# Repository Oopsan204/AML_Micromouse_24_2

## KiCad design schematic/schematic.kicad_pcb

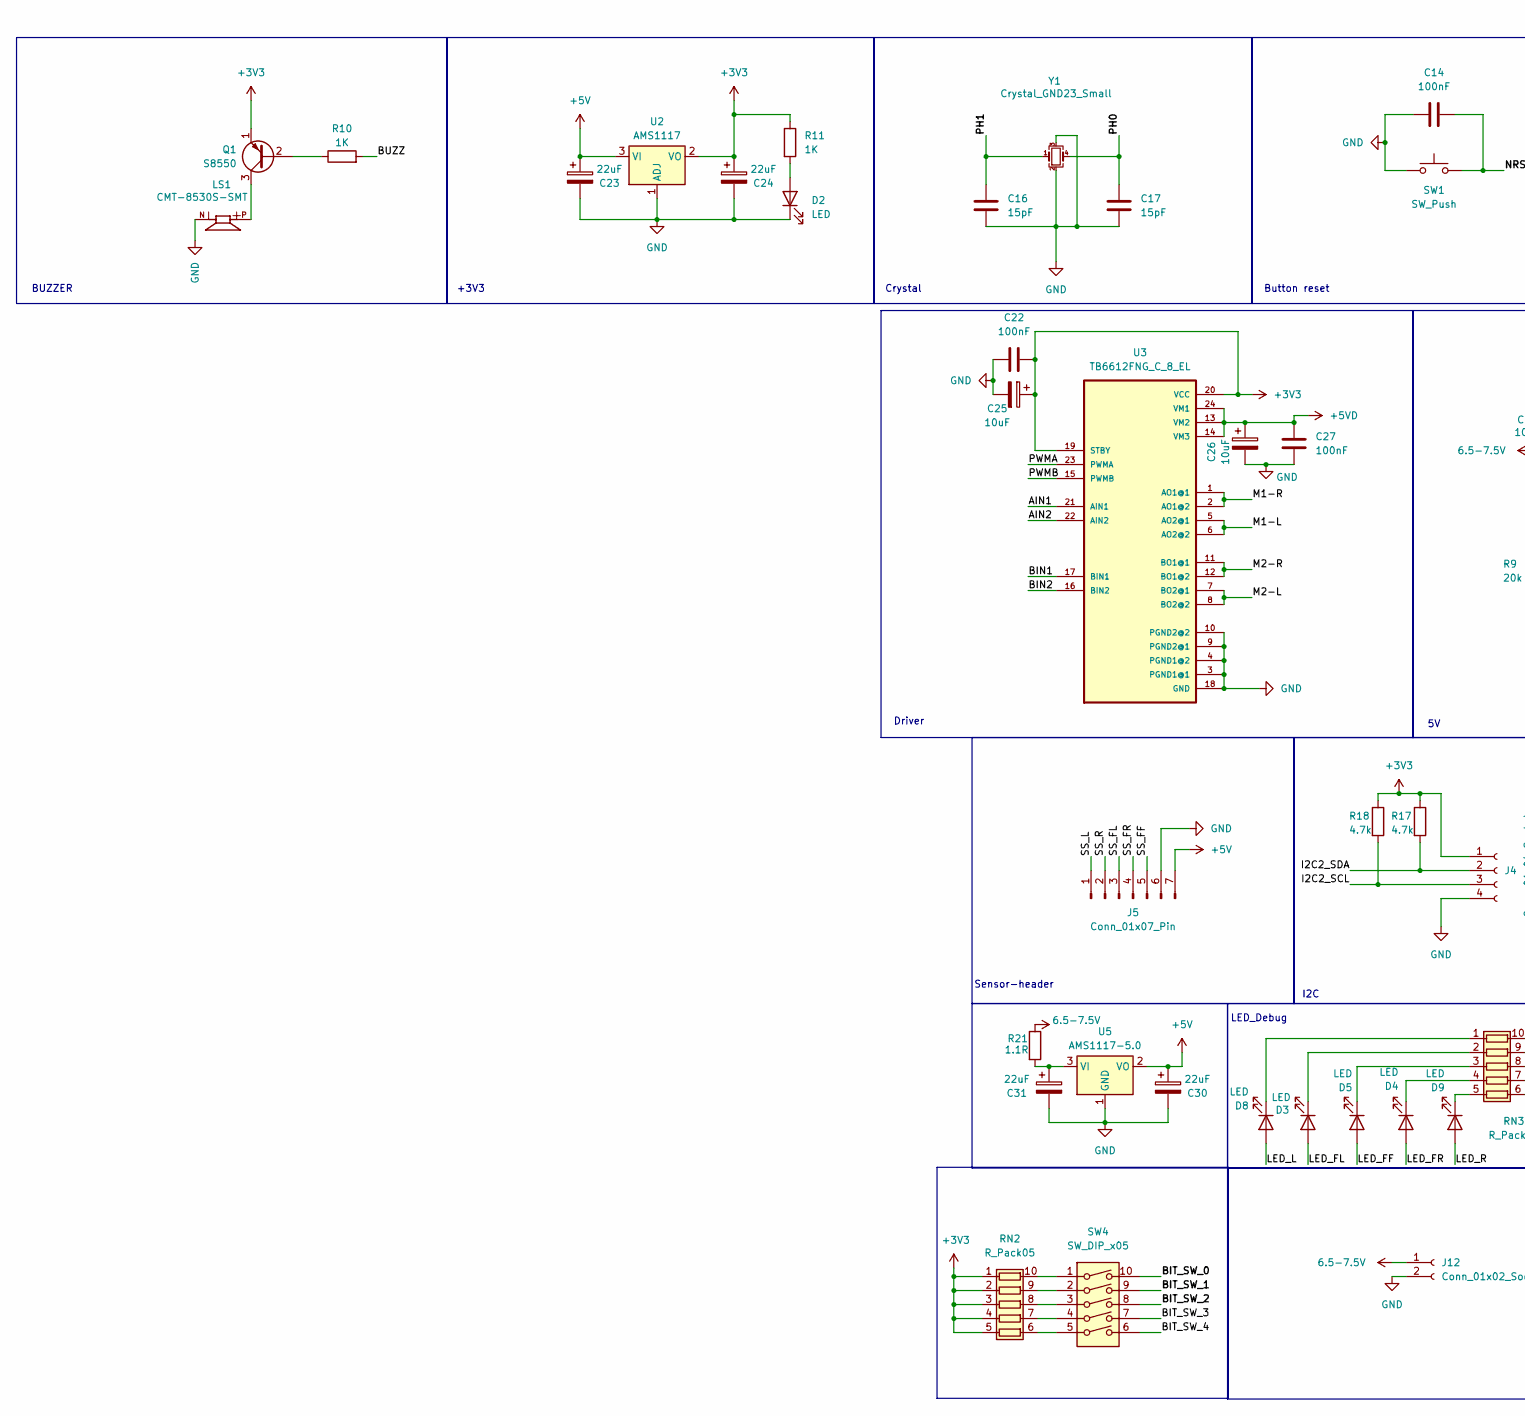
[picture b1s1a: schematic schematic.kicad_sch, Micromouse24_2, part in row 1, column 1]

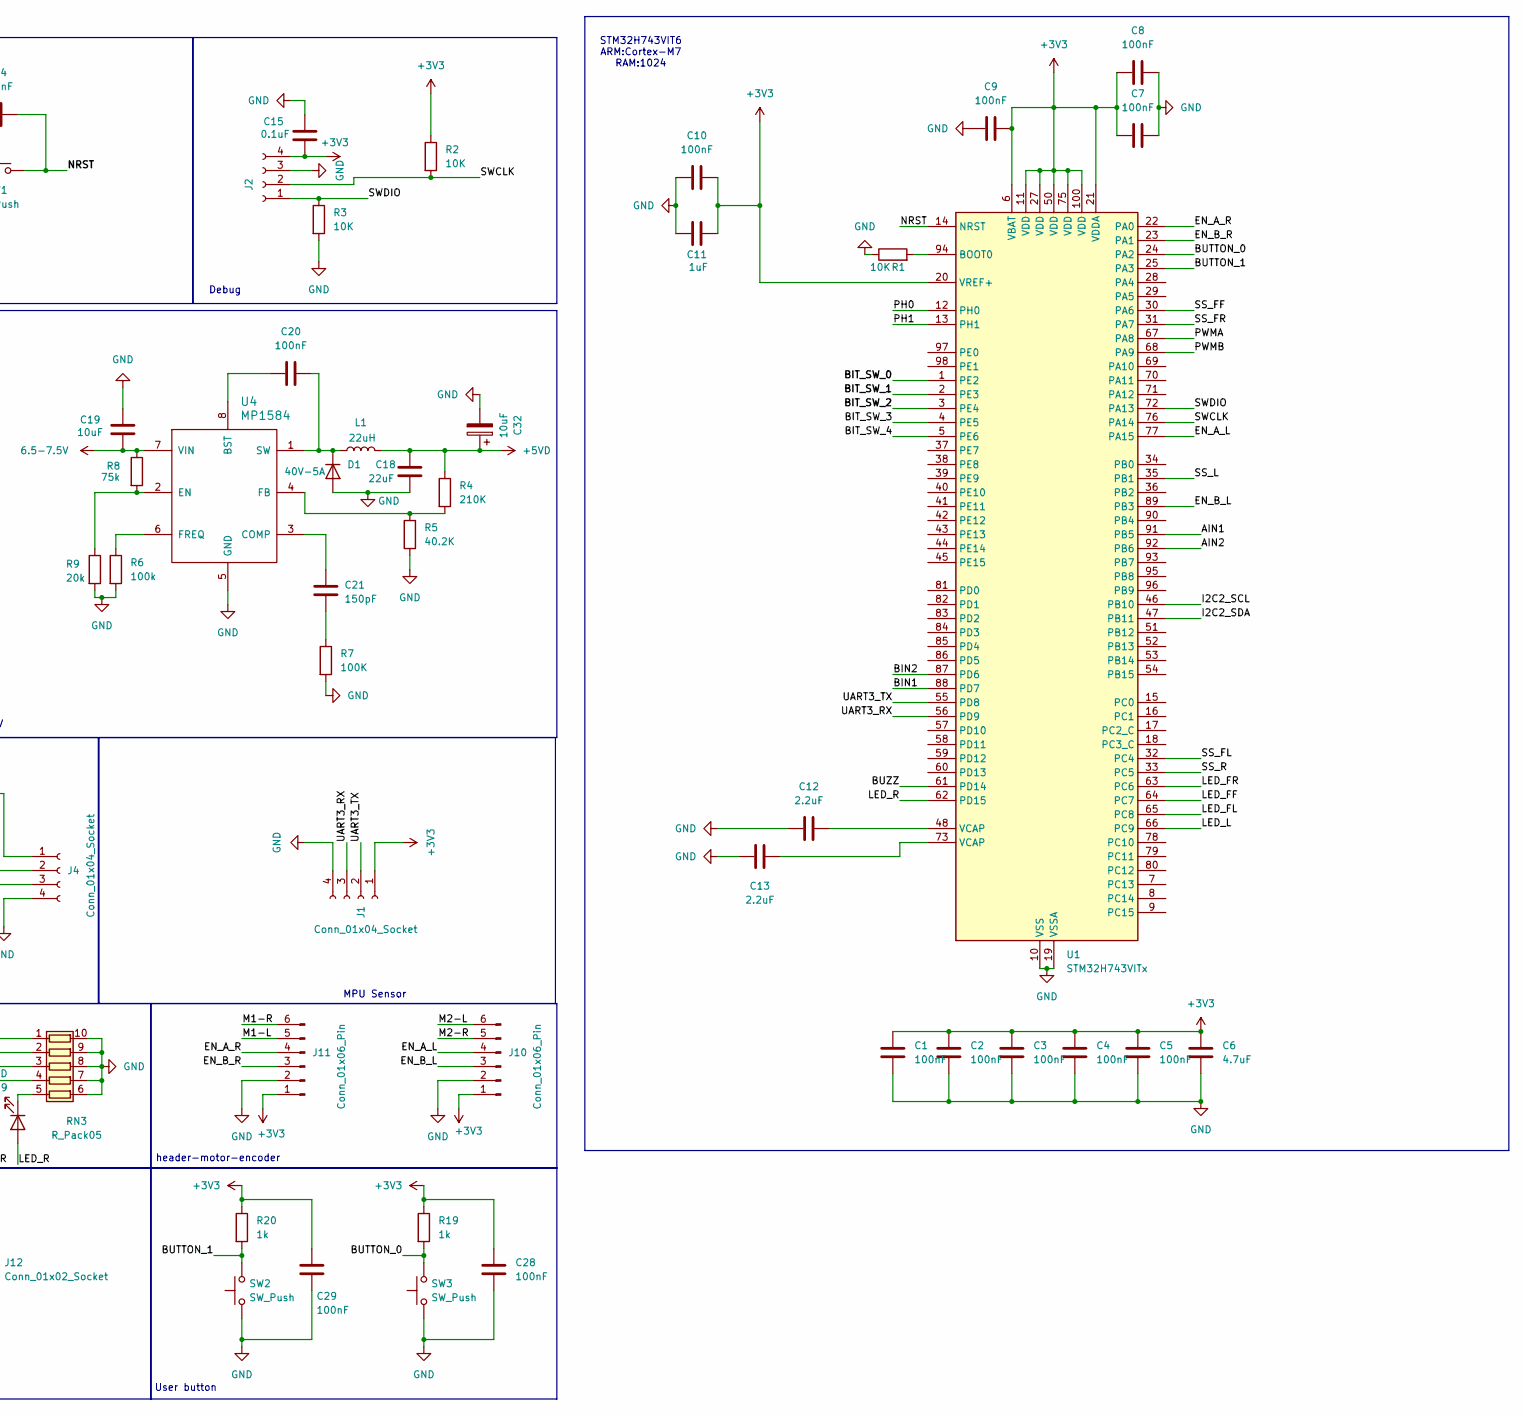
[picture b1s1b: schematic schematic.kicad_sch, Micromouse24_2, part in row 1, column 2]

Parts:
C1, C2, C3, C4, C5, C7, C8, C9, C10, C14, C20, C22, C27, C28, C29: 100nF; C_0603_1608Metric
C6: 4.7uF; C_0603_1608Metric
C11: 1uF; C_0603_1608Metric
C12, C13: 2.2uF; C_0603_1608Metric
C15: 0.1uF; C_0603_1608Metric
C16, C17: 15pF; C_0603_1608Metric
C18: 22uF; C_0603_1608Metric
C19: 10uF; C_0603_1608Metric
C21: 150pF; C_0805_2012Metric
C23, C24, C30, C31: 22uF; CP_EIA-3216-10_Kemet-I
C25, C26, C32: 10uF; CP_EIA-3216-10_Kemet-I
D1: 40V-5A; D_SMA
D2, D3, D4, D5, D8, D9: LED; LED_0603_1608Metric
J1, J2, J4: Conn_01x04_Socket; JST 4
J5: Conn_01x07_Pin; PinHeader_1x07_P2.54mm_Vertical
J10, J11: Conn_01x06_Pin; JST 6
J12: Conn_01x02_Socket; jst
L1: 22uH; L_7.3x7.3_H4.5
LS1: CMT-8530S-SMT; CUI_CMT-8530S-SMT
Q1: S8550; SOT-23
R1, R2, R3: 10K; R_0603_1608Metric
R4: 210K; R_0603_1608Metric
R5: 40.2K; R_0805_2012Metric
R6: 100k; R_0603_1608Metric
R7: 100K; R_0603_1608Metric
R8: 75k; R_0805_2012Metric
R9: 20k; R_0805_2012Metric
R10, R11: 1K; R_0603_1608Metric
R17, R18: 4.7k; R_0603_1608Metric
R19, R20: 1k; R_0603_1608Metric
R21: 1.1R; R_0805_2012Metric
RN2, RN3: R_Pack05; R_Array_Convex_5x0603
SW1, SW2, SW3: SW_Push; SW_Tactile_SPST_NO_Straight_CK_PTS636Sx25SMTRLFS
SW4: SW_DIP_x05; SW_DIP_SPSTx05_Slide_KingTek_DSHP05TS_W7.62mm_P1.27mm
U1: STM32H743VITx; LQFP-100_14x14mm_P0.5mm
U2: AMS1117; SOT-223-3_TabPin2
U3: TB6612FNG_C_8_EL; SOP65P760X160-24N
U4: MP1584; SO-08POWER
U5: AMS1117-5.0; SOT-223-3_TabPin2
Y1: Crystal_GND23_Small; Crystal_SMD_3225-4Pin_3.2x2.5mm

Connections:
6.5-7.5V: C19.2, J12.1, R8.1, R21.1, U4.7 (VIN)
+3V3: C1.1, C2.1, C3.1, C4.1, C5.1, C6.1, C7.2, C8.2, C9.1, C10.1, C11.1, C15.1, C22.1, C24.1, C25.1, C28.1, C29.1, J1.1, J2.4, J4.1, J10.1, J11.1, Q1.1 (E), R2.1, R11.1, R17.1, R18.1, R19.1, R20.1, RN2.1 (R1.1), RN2.2 (R2.1), RN2.3 (R3.1), RN2.4 (R4.1), RN2.5 (R5.1), U1.6 (VBAT), U1.11 (VDD), U1.20 (VREF+), U1.21 (VDDA), U1.27 (VDD), U1.50 (VDD), U1.75 (VDD), U1.100 (VDD), U2.2 (VO), U3.19 (STBY), U3.20 (VCC); also elsewhere on the board
+5V: C23.1, C30.1, J5.7, U2.3 (VI), U5.2 (VO)
+5VD: C18.1, C26.1, C27.1, C32.1, L1.2, R4.1, U3.13 (VM2), U3.14 (VM3), U3.24 (VM1)
/AIN1: U1.91 (PB5), U3.21 (AIN1)
/AIN2: U1.92 (PB6), U3.22 (AIN2)
/BIN1: U1.88 (PD7), U3.17 (BIN1)
/BIN2: U1.87 (PD6), U3.16 (BIN2)
/BIT_SW_0: SW4.10, U1.1 (PE2)
/BIT_SW_1: SW4.9, U1.2 (PE3)
/BIT_SW_2: SW4.8, U1.3 (PE4)
/BIT_SW_3: SW4.7, U1.4 (PE5)
/BIT_SW_4: SW4.6, U1.5 (PE6)
/BUTTON_0: R19.2, SW3.2, U1.24 (PA2)
/BUTTON_1: R20.2, SW2.2, U1.25 (PA3)
/BUZZ: R10.2, U1.61 (PD14)
/EN_A_L: J10.4, U1.77 (PA15); also elsewhere on the board
/EN_A_R: J11.4, U1.22 (PA0); also elsewhere on the board
/EN_B_L: J10.3, U1.89 (PB3); also elsewhere on the board
/EN_B_R: J11.3, U1.23 (PA1); also elsewhere on the board
/I2C2_SCL: J4.3, R18.2, U1.46 (PB10); also elsewhere on the board
/I2C2_SDA: J4.2, R17.2, U1.47 (PB11); also elsewhere on the board
/LED_FF: D5.2 (A), U1.64 (PC7)
/LED_FL: D3.2 (A), U1.65 (PC8)
/LED_FR: D4.2 (A), U1.63 (PC6)
/LED_L: D8.2 (A), U1.66 (PC9)
/LED_R: D9.2 (A), U1.62 (PD15)
/M1-L: J11.5, U3.5 (AO2@1), U3.6 (AO2@2); also elsewhere on the board
/M1-R: J11.6, U3.1 (AO1@1), U3.2 (AO1@2); also elsewhere on the board
/M2-L: J10.6, U3.7 (BO2@1), U3.8 (BO2@2); also elsewhere on the board
/M2-R: J10.5, U3.11 (BO1@1), U3.12 (BO1@2); also elsewhere on the board
/NRST: C14.2, SW1.2, U1.14 (NRST); also elsewhere on the board
/PH0: C17.1, U1.12 (PH0), Y1.4
/PH1: C16.1, U1.13 (PH1), Y1.1
/PWMA: U1.67 (PA8), U3.23 (PWMA)
/PWMB: U1.68 (PA9), U3.15 (PWMB)
/SS_FF: J5.5, U1.30 (PA6)
/SS_FL: J5.3, U1.32 (PC4)
/SS_FR: J5.4, U1.31 (PA7)
/SS_L: J5.1, U1.35 (PB1)
/SS_R: J5.2, U1.33 (PC5)
/SWCLK: J2.2, R2.2, U1.76 (PA14); also elsewhere on the board
/SWDIO: J2.1, R3.1, U1.72 (PA13); also elsewhere on the board
/UART3_RX: J1.3, U1.56 (PD9)
/UART3_TX: J1.2, U1.55 (PD8)
GND: C1.2, C2.2, C3.2, C4.2, C5.2, C6.2, C7.1, C8.1, C9.2, C10.2, C11.2, C12.2, C13.2, C14.1, C15.2, C16.2, C17.2, C18.2, C19.1, C22.2, C23.2, C24.2, C25.2, C26.2, C27.2, C28.2, C29.2, C30.2, C31.2, C32.2, D1.2 (A), D2.1 (K), J1.4, J2.3, J4.4, J5.6, J10.2, J11.2, J12.2, LS1.N, R1.1, R3.2, R5.1, R6.2, R7.2, R9.2, RN3.6 (R5.2), RN3.7 (R4.2), RN3.8 (R3.2), RN3.9 (R2.2), RN3.10 (R1.2), SW1.1, SW2.1, SW3.1, U1.10 (VSS), U1.19 (VSSA), U1.26 (VSS), U1.49 (VSS), U1.74 (VSS), U1.99 (VSS), U2.1 (ADJ), U3.3 (PGND1@1), U3.4 (PGND1@2), U3.9 (PGND2@1), U3.10 (PGND2@2), U3.18 (GND), U4.5 (GND), U5.1 (GND), Y1.2, Y1.3; also elsewhere on the board
unnamed: C12.1, U1.48 (VCAP)
unnamed: C13.1, U1.73 (VCAP)
unnamed: C21.2, R7.1
unnamed: C20.2, D1.1 (K), L1.1, U4.1 (SW)
unnamed: D2.2 (A), R11.2
unnamed: D3.1 (K), RN3.2 (R2.1)
unnamed: D4.1 (K), RN3.4 (R4.1)
unnamed: D5.1 (K), RN3.3 (R3.1)
unnamed: D8.1 (K), RN3.1 (R1.1)
unnamed: D9.1 (K), RN3.5 (R5.1)
unnamed: Q1.2 (B), R10.1
unnamed: LS1.P, Q1.3 (C)
unnamed: RN2.10 (R1.2), SW4.1
unnamed: RN2.9 (R2.2), SW4.2
unnamed: RN2.8 (R3.2), SW4.3
unnamed: RN2.7 (R4.2), SW4.4
unnamed: RN2.6 (R5.2), SW4.5
unnamed: R1.2, U1.94 (BOOT0)
unnamed: C20.1, U4.8 (BST)
unnamed: C21.1, U4.3 (COMP)
unnamed: R8.2, R9.1, U4.2 (EN)
unnamed: R4.2, R5.2, U4.4 (FB)
unnamed: R6.1, U4.6 (FREQ)
unnamed: C31.1, R21.2, U5.3 (VI)

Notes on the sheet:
MPU Sensor
User button
+3V3
Debug
STM32H743VIT6 ARM:Cortex-M7 RAM:1024
LED_Debug
Sensor-header
BUZZER
I2C
Driver
Button reset
header-motor-encoder
Crystal

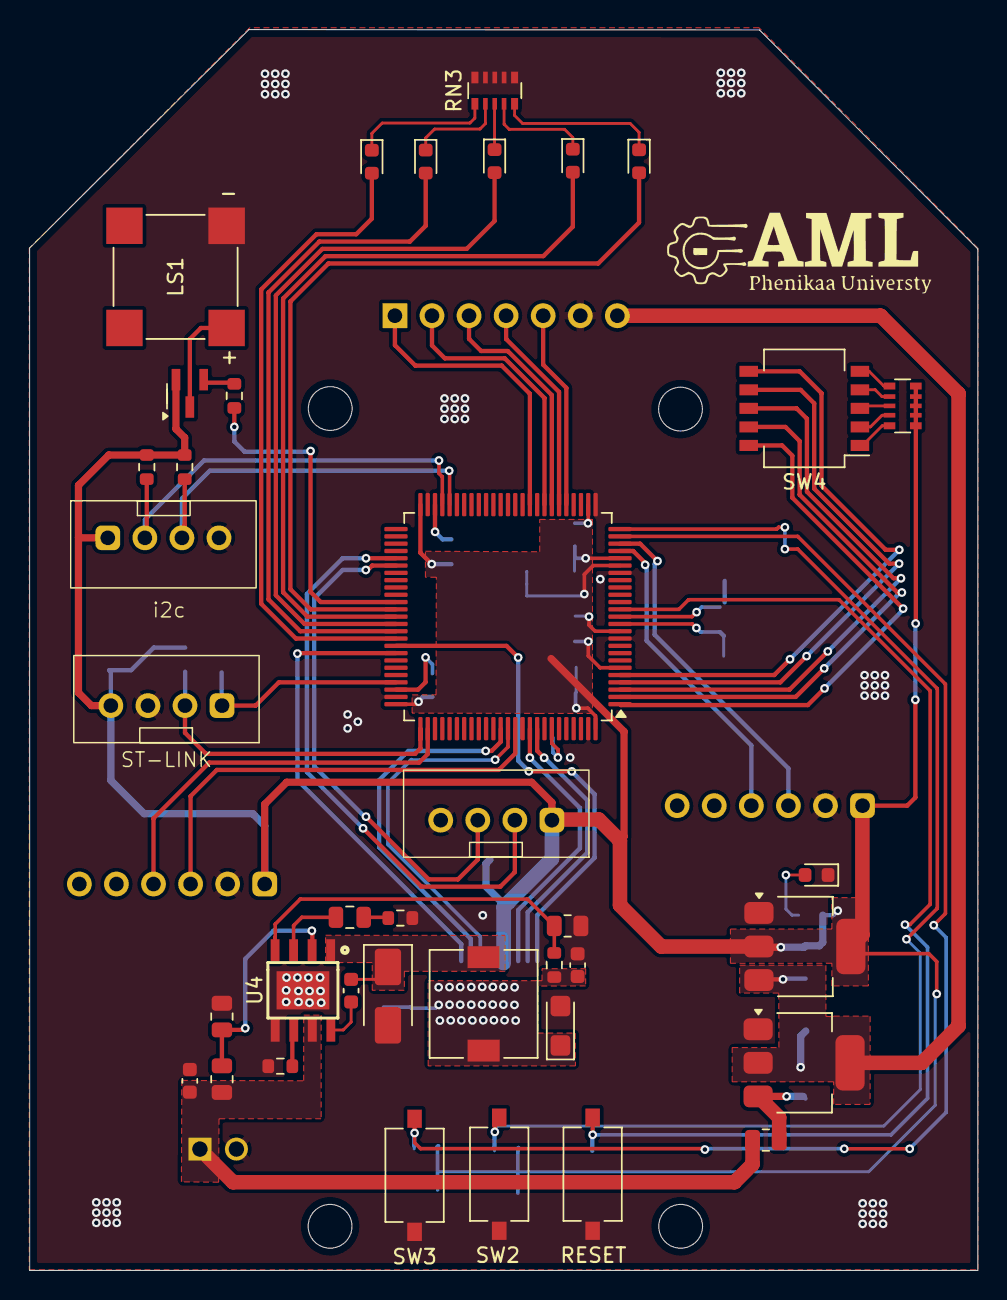
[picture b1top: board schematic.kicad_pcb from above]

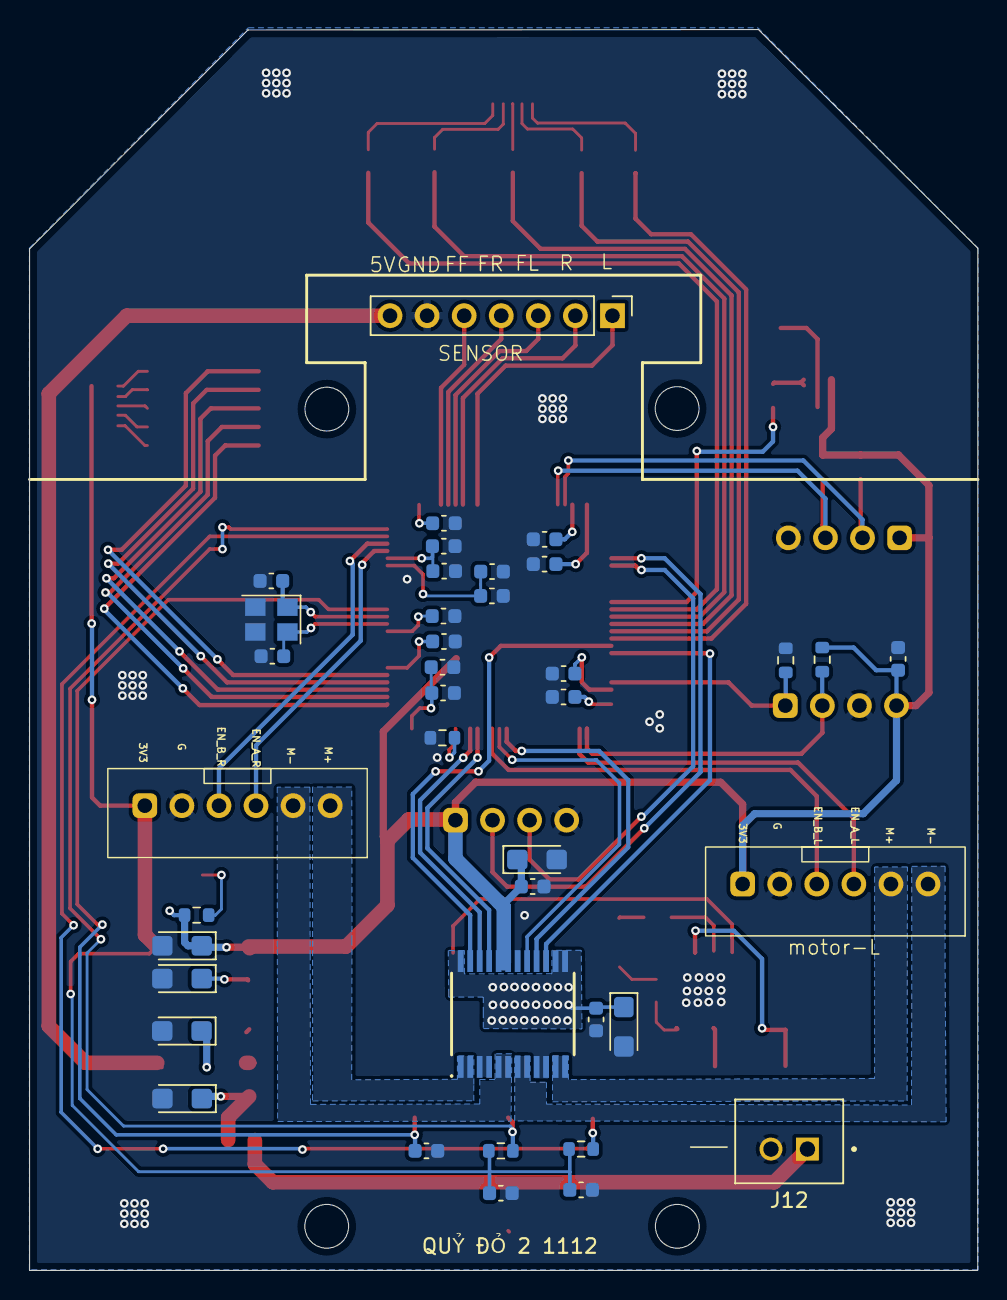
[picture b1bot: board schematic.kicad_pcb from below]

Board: 2 copper layers, 65.0 x 85.0 mm, 77 parts (39 on the bottom side), 70 nets.

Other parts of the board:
RESET: SW_Push; SW_Tactile_SPST_NO_Straight_CK_PTS636Sx25SMTRLFS
ST-LINK: Conn_01x04_Socket; JST 4
i2c: Conn_01x04_Socket; JST 4
moter-r: Conn_01x06_Pin; JST 6
motor-L: Conn_01x06_Pin; JST 6

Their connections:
+3V3: ST-LINK.4, i2c.1, moter-r.1, motor-L.1; also elsewhere on the board
/EN_A_L: motor-L.4; also elsewhere on the board
/EN_A_R: moter-r.4; also elsewhere on the board
/EN_B_L: motor-L.3; also elsewhere on the board
/EN_B_R: moter-r.3; also elsewhere on the board
/I2C2_SCL: i2c.3; also elsewhere on the board
/I2C2_SDA: i2c.2; also elsewhere on the board
/M1-L: moter-r.5; also elsewhere on the board
/M1-R: moter-r.6; also elsewhere on the board
/M2-L: motor-L.6; also elsewhere on the board
/M2-R: motor-L.5; also elsewhere on the board
/NRST: RESET.2; also elsewhere on the board
/SWCLK: ST-LINK.2; also elsewhere on the board
/SWDIO: ST-LINK.1; also elsewhere on the board
GND: RESET.1, ST-LINK.3, i2c.4, moter-r.2, motor-L.2; also elsewhere on the board

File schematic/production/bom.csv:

Designator,Footprint,Quantity,Value,LCSC Part #
"C1, C10, C14, C2, C20, C22, C27, C28, C29, C3, C4, C5, C7, C8, C9",0603,15,100nF,
C11,0603,1,1uF,
"C12, C13",0603,2,2.2uF,
C15,0603,1,0.1uF,
"C16, C17",0603,2,15pF,
C18,0603,1,22uF,
C19,0603,1,10uF,
C21,0805,1,150pF,
"C23, C24, C30, C31",CP_EIA-3216-10_Kemet-I,4,22uF,
"C25, C26, C32",CP_EIA-3216-10_Kemet-I,3,10uF,
C6,0603,1,4.7uF,
D1,D_SMA,1,40V-5A,
"D2, D3, D4, D5, D8, D9",0603,6,LED,
"I2C, J1, ST-LINK",JST 4,3,Conn_01x04_Socket,
J12,jst,1,Conn_01x02_Socket,
J5,PinHeader_1x07_P2.54mm_Vertical,1,Conn_01x07_Pin,
L1,L_7.3x7.3_H4.5,1,22uH,
LS1,CUI_CMT-8530S-SMT,1,CMT-8530S-SMT,
"MOTER-R, MOTOR-L",JST 6,2,Conn_01x06_Pin,
Q1,SOT-23,1,S8550,
"R1, R2, R3",0603,3,10K,
"R10, R11, R19, R20",0603,4,1K,
"R17, R18",0603,2,4.7k,
R21,0805,1,1.1R,
R4,0603,1,210K,
R5,0805,1,40.2K,
"R6, R7",0603,2,100k,
R8,0805,1,75k,
R9,0805,1,20k,
"RESET, SW2, SW3",SW_Tactile_SPST_NO_Straight_CK_PTS636Sx25SMTRLFS,3,SW_Push,
"RN2, RN3",R_Array_Convex_5x0603,2,R_Pack05,
SW4,SW_DIP_SPSTx05_Slide_KingTek_DSHP05TS_W7.62mm_P1.27mm,1,SW_DIP_x05,
U1,LQFP-100_14x14mm_P0.5mm,1,STM32H743VITx,
U2,SOT-223-3_TabPin2,1,AMS1117,
U3,SOP65P760X160-24N,1,TB6612FNG_C_8_EL,
U4,SO-08POWER,1,MP1584,
U5,SOT-223-3_TabPin2,1,AMS1117-5.0,
Y1,Crystal_SMD_3225-4Pin_3.2x2.5mm,1,Crystal_GND23_Small,

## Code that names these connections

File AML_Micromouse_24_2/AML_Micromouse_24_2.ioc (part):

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Mcu.Name=STM32H743VITx
Mcu.Package=LQFP100
Mcu.UserName=STM32H743VITx
PA0.GPIOParameters=GPIO_Label
PA0.GPIO_Label=EN_A_R
PA0.Signal=S_TIM5_CH1
PA1.GPIOParameters=GPIO_Label
PA1.GPIO_Label=EN_B_L
PA1.Signal=S_TIM5_CH2
PA13\ (JTMS/SWDIO).Mode=Serial_Wire
PA13\ (JTMS/SWDIO).Signal=DEBUG_JTMS-SWDIO
PA14\ (JTCK/SWCLK).Mode=Serial_Wire
PA14\ (JTCK/SWCLK).Signal=DEBUG_JTCK-SWCLK
PA15\ (JTDI).GPIOParameters=GPIO_Label
PA15\ (JTDI).GPIO_Label=EN_A_L
PA15\ (JTDI).Signal=S_TIM2_CH1_ETR
PA2.GPIOParameters=GPIO_Label
PA2.GPIO_Label=BUTTON_0
PA2.Signal=GPIO_Input
PA3.GPIOParameters=GPIO_Label
PA3.GPIO_Label=BUTTON_1
PA3.Signal=GPIO_Input
PA6.GPIOParameters=GPIO_Label
PA6.GPIO_Label=SS_FF
PA6.Signal=ADCx_INP3
PA7.GPIOParameters=GPIO_Label
PA7.GPIO_Label=SS_FR
PA7.Signal=ADCx_INP7
PA8.GPIOParameters=GPIO_Label
PA8.GPIO_Label=PWMA
PA8.Signal=S_TIM1_CH1
PA9.GPIOParameters=GPIO_Label
PA9.GPIO_Label=PWMB
PA9.Signal=S_TIM1_CH2
PB1.GPIOParameters=GPIO_Label
PB1.GPIO_Label=SS_L
PB1.Signal=ADCx_INP5
PB10.Mode=I2C
PB10.Signal=I2C2_SCL
PB11.Mode=I2C
PB11.Signal=I2C2_SDA
PB3\ (JTDO/TRACESWO).GPIOParameters=GPIO_Label
PB3\ (JTDO/TRACESWO).GPIO_Label=EN_B_L
PB3\ (JTDO/TRACESWO).Signal=S_TIM2_CH2
PB5.GPIOParameters=GPIO_Label
PB5.GPIO_Label=AIN1
PB5.Signal=GPIO_Output
PB6.GPIOParameters=GPIO_Label
PB6.GPIO_Label=AIN2
PB6.Signal=GPIO_Output
PC4.GPIOParameters=GPIO_Label
PC4.GPIO_Label=SS_FL
PC4.Signal=ADCx_INP4
PC5.GPIOParameters=GPIO_Label
PC5.GPIO_Label=SS_R
PC5.Signal=ADCx_INP8
PC6.GPIOParameters=GPIO_PuPd,GPIO_Label
PC6.GPIO_Label=LED_1
PC6.GPIO_PuPd=GPIO_NOPULL
PC6.Signal=GPIO_Output
PC7.GPIOParameters=GPIO_Label
PC7.GPIO_Label=LED_2
PC7.Signal=GPIO_Output
PC8.GPIOParameters=GPIO_Label
PC8.GPIO_Label=LED_3
PC8.Signal=GPIO_Output
PC9.GPIOParameters=GPIO_Label
PC9.GPIO_Label=LED_4
PC9.Signal=GPIO_Output
PD14.GPIOParameters=GPIO_Label
PD14.GPIO_Label=buzzer
PD14.Signal=S_TIM4_CH3
PD15.GPIOParameters=GPIO_Label
PD15.GPIO_Label=LED_0
PD15.Signal=GPIO_Output
PD6.GPIOParameters=GPIO_Label
PD6.GPIO_Label=BIN2
PD6.Signal=GPIO_Output
PD7.GPIOParameters=GPIO_Label
PD7.GPIO_Label=BIN1
PD7.Signal=GPIO_Output
PD8.Mode=Asynchronous
PD8.Signal=USART3_TX
PD9.Mode=Asynchronous
PD9.Signal=USART3_RX
PE2.GPIOParameters=GPIO_PuPd,GPIO_Label
PE2.GPIO_Label=BIT_SW_0
PE2.GPIO_PuPd=GPIO_PULLDOWN
PE2.Signal=GPIO_Input
PE3.GPIOParameters=GPIO_PuPd,GPIO_Label
PE3.GPIO_Label=BIT_SW_1
PE3.GPIO_PuPd=GPIO_PULLDOWN
PE3.Signal=GPIO_Input
PE4.GPIOParameters=GPIO_PuPd,GPIO_Label
PE4.GPIO_Label=BIT_SW_2
PE4.GPIO_PuPd=GPIO_PULLDOWN
PE4.Signal=GPIO_Input
PE5.GPIOParameters=GPIO_PuPd,GPIO_Label
PE5.GPIO_Label=BIT_SW_3
PE5.GPIO_PuPd=GPIO_PULLDOWN
PE5.Signal=GPIO_Input
PE6.GPIOParameters=GPIO_PuPd,GPIO_Label
PE6.GPIO_Label=BIT_SW_4
PE6.GPIO_PuPd=GPIO_PULLDOWN
PE6.Signal=GPIO_Input
PH0-OSC_IN\ (PH0).Mode=HSE-External-Oscillator
PH0-OSC_IN\ (PH0).Signal=RCC_OSC_IN
PH1-OSC_OUT\ (PH1).Mode=HSE-External-Oscillator
PH1-OSC_OUT\ (PH1).Signal=RCC_OSC_OUT
RCC.HSE_VALUE=25000000
RCC.SYSCLKFreq_VALUE=480000000
RCC.SYSCLKSource=RCC_SYSCLKSOURCE_PLLCLK
board=custom

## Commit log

2024-08-17 1.2%
2024-08-28 no message
2024-08-31 vẽ xong phần cơ bản
2024-09-05 thêm phần driver tb66, ve phần nguồn 5v
2024-09-06 xong phần nguồn
2024-09-07 vẽ đủ đò ăn chơi chưa duyệt
2024-09-07 thếu nút nhấn
2024-09-13 trc khi xoá ve lai
2024-10-19 gần hoàn thiện pcb
2024-10-20 cho doi xi va
2024-10-22 khá ổn chờ chốt
2024-10-23 thêm file thiet ke va da chinh sua nhung chua chot
2024-10-24 đã đặt mạch
2024-10-28 thư viện đọc sensor analog
2024-11-05 test pcb hoạt động adc+mpu+bitsw+button
2024-11-07 đổi sang cmake
2024-11-19 the ends
2024-11-29 đã build được bằng cmake và đang viết hàm bám trường rẽ trái rẽ phải
2024-11-29 test
2024-11-30 test 2
2024-12-25 trc khi do che
2025-01-02 medianfilter
2025-01-24 bản chạy ok phai chinh nhieu dieu khien
2025-02-08 chay tam on
2025-02-18 doi ham reset mpu moi
2025-02-22 chay kha ok trc khi doi co che lay bang tin mpu
